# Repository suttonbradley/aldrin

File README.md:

# Aldrin Keyboard
Split keyboard designed using ergogen. Inspired by Christian Selig's [dream keyboard video](https://www.youtube.com/watch?v=7UXsD7nSfDY).

## ZMK config
ZMK config for this keyboard is in a separate repo [here](https://github.com/suttonbradley/aldrin-zmk), for the sake of getting firmware from GitHub Actions

## Sourced parts
- [Typeractive](typeractive.xyz)
    - nice!nano
    - Power switch
    - Reset button
    - MX hotswap sockets
    - SMD diodes
    - Machine sockets/pins
    - Battery jack
- PS3 batteries from [Amazon](https://www.amazon.com/dp/B09726K2LC)
- PCBs from [JLCPCB](jlcpcb.com)

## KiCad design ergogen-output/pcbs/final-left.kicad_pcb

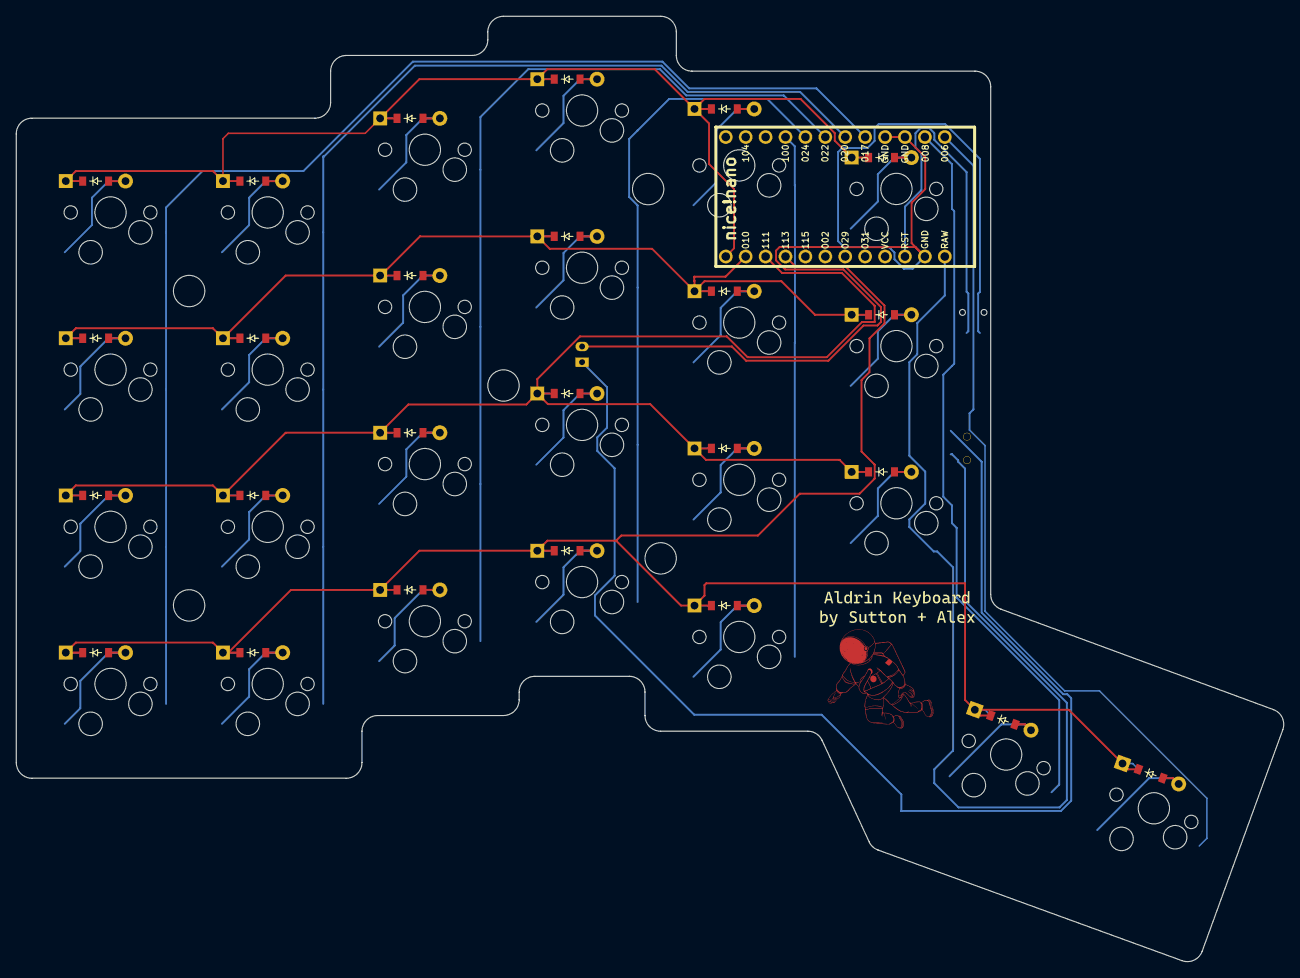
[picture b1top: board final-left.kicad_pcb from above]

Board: 2 copper layers, 161.7 x 120.6 mm, 54 parts (0 on the bottom side), 40 nets.

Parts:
B1: Panasonic_EVQPUL_EVQPUC
D1, D2, D3, D4, D5, D6, D7, D8, D9, D10, D11, D12, D13, D14, D15, D16, D17, D18, D19, D20, D21, D22, D23, D24, D25: ComboDiode
JST1: JST_PH_S2B-PH-K_02x2.00mm_Angled
MCU1: nice_nano
S1, S2, S3, S4, S5, S6, S7, S8, S9, S10, S11, S12, S13, S14, S15, S16, S17, S18, S19, S20, S21, S22, S23, S24, S25: MX
T1: SPDT_C128955

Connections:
GND: B1.1, JST1.2, MCU1.3, MCU1.4, MCU1.23
P006: MCU1.1, S25.1
P008: MCU1.2, S21.1, S22.1, S23.1, S24.1
P009: D4.1, D8.1, D12.1, D16.1, D22.1, D25.1, MCU1.13
P010: D3.1, D7.1, D11.1, D15.1, D19.1, D21.1, MCU1.14
P017: MCU1.5, S1.1, S2.1, S3.1, S4.1
P020: MCU1.6, S5.1, S6.1, S7.1, S8.1
P022: MCU1.7, S9.1, S10.1, S11.1, S12.1
P024: MCU1.8, S13.1, S14.1, S15.1, S16.1
P100: MCU1.9, S17.1, S18.1, S19.1, S20.1
P111: D2.1, D6.1, D10.1, D14.1, D18.1, D20.1, MCU1.15
P113: D1.1, D5.1, D9.1, D13.1, D17.1, D23.1, D24.1, MCU1.16
RAW: MCU1.24, T1.2
RST: B1.2, MCU1.22
index_bottom: D18.2, S18.2
index_home: D19.2, S19.2
index_mod: D17.2, S17.2
index_top: D25.2, S20.2
inner_bottom: D20.2, S21.2
inner_first: D23.2, S24.2
inner_home: D21.2, S22.2
inner_top: D22.2, S23.2
middle_bottom: D14.2, S14.2
middle_home: D15.2, S15.2
middle_mod: D13.2, S13.2
middle_top: D16.2, S16.2
outer_bottom: D2.2, S2.2
outer_first: D24.2, S25.2
outer_home: D3.2, S3.2
outer_mod: D1.2, S1.2
outer_top: D4.2, S4.2
pinky_bottom: D6.2, S6.2
pinky_home: D7.2, S7.2
pinky_mod: D5.2, S5.2
pinky_top: D8.2, S8.2
pos: JST1.1, T1.1
ring_bottom: D10.2, S10.2
ring_home: D11.2, S11.2
ring_mod: D9.2, S9.2
ring_top: D12.2, S12.2

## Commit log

2024-08-01 Initial commit - add config v1
2024-08-02 Reduce key layout to 50, eliminating innerinner col and num row
2024-08-02 Switch to 1u thumb keys
2024-08-02 Adjust spacing of thumb cluster
2024-08-06 -14 shift on thumb cluster
2024-08-06 -12 shift on thumb cluster
2024-08-07 Start PCB
2024-08-07 Move into ergogen dir
2024-08-07 Add nice_nano footprint
2024-08-07 Use nice nano footprint with no pins or holes for 101, 102, or 107
2024-08-08 Add in footprints for diodes/battery jack/reset switch/battery switch/mounting holes, reduce pad around edge of PCB, use U instead of u
2024-08-08 Add spacing
2024-08-08 Make PCB follow bottom of key layout closely
2024-08-08 battery switch placement
2024-08-08 Misc
2024-08-08 Set up column and row nets
2024-08-08 Right half PCB
2024-08-12 Final
2024-08-12 Switch around pin hole matching for easier routing
2024-08-12 Fix some stuff specific to right PCB, final pass at pin assignment?
2024-08-12 Add PCB output post-PCB order
2024-08-13 fix pcbs :(
2024-08-13 Ignore gerber files
2024-08-13 fix pcbs part 2
2024-08-13 Fix up PCB one last time
2024-08-13 Make ergogen line up mounting hole with where it was manually adjusted to in kicad
2024-08-13 add .github
2024-08-13 ZMK first crack
2024-08-13 Use my zmk fork
2024-08-13 fix dir structure
2024-08-13 Fix west.yml
2024-08-13 Go back to my zmk fork
2024-08-13 Copy from discrete zmk repo
2024-08-13 Try my fork of zmk
2024-08-13 trigger pipeline
2024-08-13 try fixing build.yml
2024-08-13 config_path
2024-08-17 Remove TODOs as PCBs is now ordered
2024-08-17 Format
2024-08-17 Add XL board and cutouts
2024-08-17 Add simplified board option (flat bottom edge)
2024-08-17 Add ergogen output
2024-08-17 Add jscad -> stl conversion
2024-08-17 Add note about github actions
2024-08-17 Add parts list
2025-06-23 adjust spacing, stagger, and thumb cluster
2025-06-23 fix up for board changes
2025-06-23 fix upu pt 2
2025-06-23 erase xl board
2025-06-24 adjust add-on components
2025-06-24 modified output
2025-06-24 plate shenanigans
